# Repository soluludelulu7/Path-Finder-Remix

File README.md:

Path Finder Remix by Svanik

Description:
Made a PCB Schematic with 5 LED's, 5 buttons, 5 resistors, and a XIAO. Then, converted schematic into PCB; routed lines and added 3D files to create a complete image. Also, wrote the code to make the LED blink 5 times when the button is pressed. My motivation to make this project was to learn PCB design and desgin my own PCB from scratch. I learned everything I know abut PCB design from this project and it was a very fun experience.

| Name      | Purpose                              | Quantity | Total Cost (USD) | Link | Distributor |
|-----------|--------------------------------------|----------|------------------|------|-------------|
| Resistors | to restrict flow of current (not buying) | 1 | $5.99 | https://www.amazon.com/Resistor-Resistors-Assortment-Breadboard-Electronics/dp/B0F4P352BB | Amazon |
| LED       | to display (not buying)             | 1 | $7.99 | https://www.microcenter.com/product/427703/5mm_Round_Multi-Colored_LED_Assortment_Set_-_25_Pack | Microcenter |
| PCB       | to solder on                        | 5 | $4.90 | https://jlcpcb.com/ | JLCPCB |
| Buttons   | to click                            | 10 | $4.99 | https://www.amazon.com/BlingKingdom-Replacement-Mechanical-Keyboard-Dustproof/dp/B0DSHTPSL3 | Amazon |
| XIAO      | to control                          | 1 | $9.99 | https://www.amazon.com/Microcontroller-Dual-Core-MicroPython-CircuitPython-Interfaces/dp/B09NNVNW7M | Amazon |

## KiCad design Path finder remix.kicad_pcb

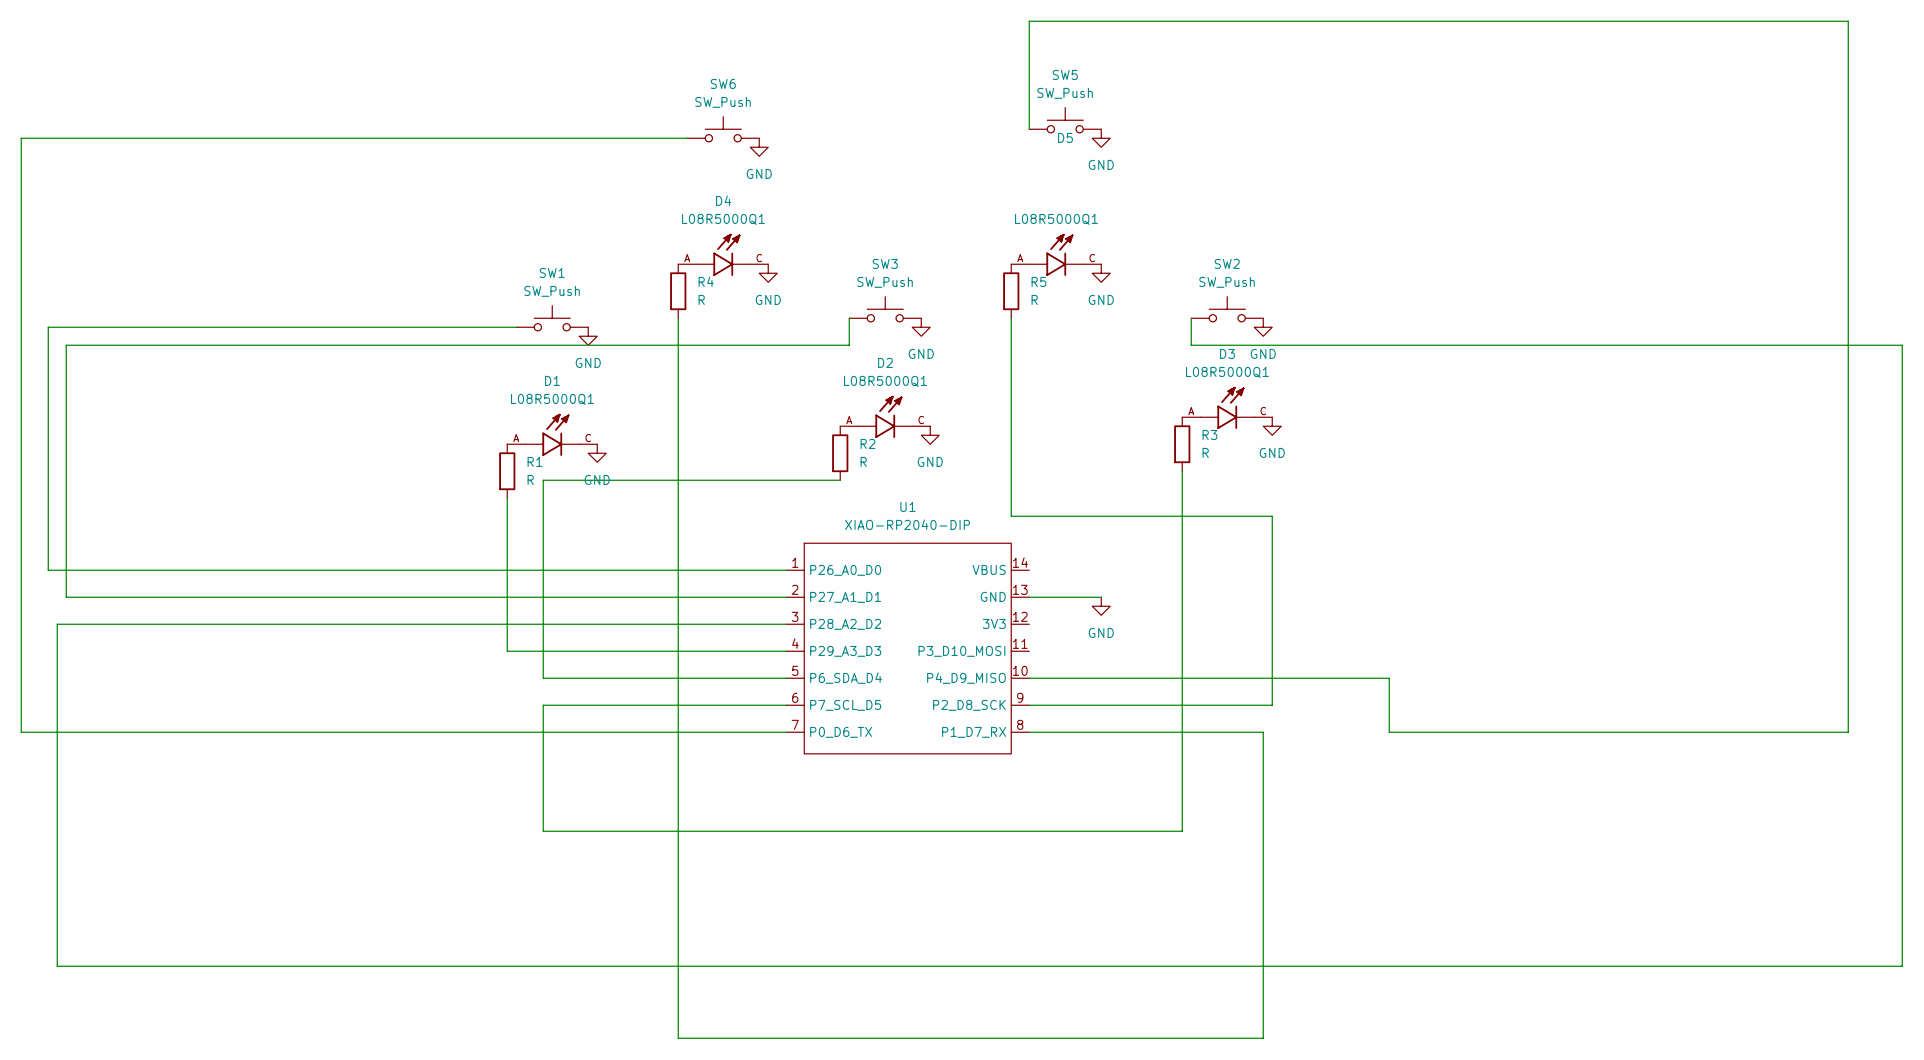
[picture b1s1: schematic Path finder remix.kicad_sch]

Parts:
D1, D2, D3, D4, D5: L08R5000Q1; LEDRD254W57D500H1070; PARTREV NA
R1, R2, R3, R4, R5: R; R_Axial_DIN0204_L3.6mm_D1.6mm_P5.08mm_Horizontal
SW1, SW2, SW3, SW5, SW6: SW_Push; SW_Cherry_MX_1.00u_PCB
U1: XIAO-RP2040-DIP

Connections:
GND: D1.C, D2.C, D3.C, D4.C, D5.C, SW1.2, SW2.2, SW3.2, SW5.2, SW6.2, U1.13 (GND)
unnamed: D1.A, R1.1
unnamed: D2.A, R2.1
unnamed: D3.A, R3.1
unnamed: D4.A, R4.1
unnamed: D5.A, R5.1
unnamed: SW6.1, U1.7 (P0_D6_TX)
unnamed: R4.2, U1.8 (P1_D7_RX)
unnamed: R5.2, U1.9 (P2_D8_SCK)
unnamed: SW5.1, U1.10 (P4_D9_MISO)
unnamed: R2.2, U1.5 (P6_SDA_D4)
unnamed: R3.2, U1.6 (P7_SCL_D5)
unnamed: SW1.1, U1.1 (P26_A0_D0)
unnamed: SW3.1, U1.2 (P27_A1_D1)
unnamed: SW2.1, U1.3 (P28_A2_D2)
unnamed: R1.2, U1.4 (P29_A3_D3)

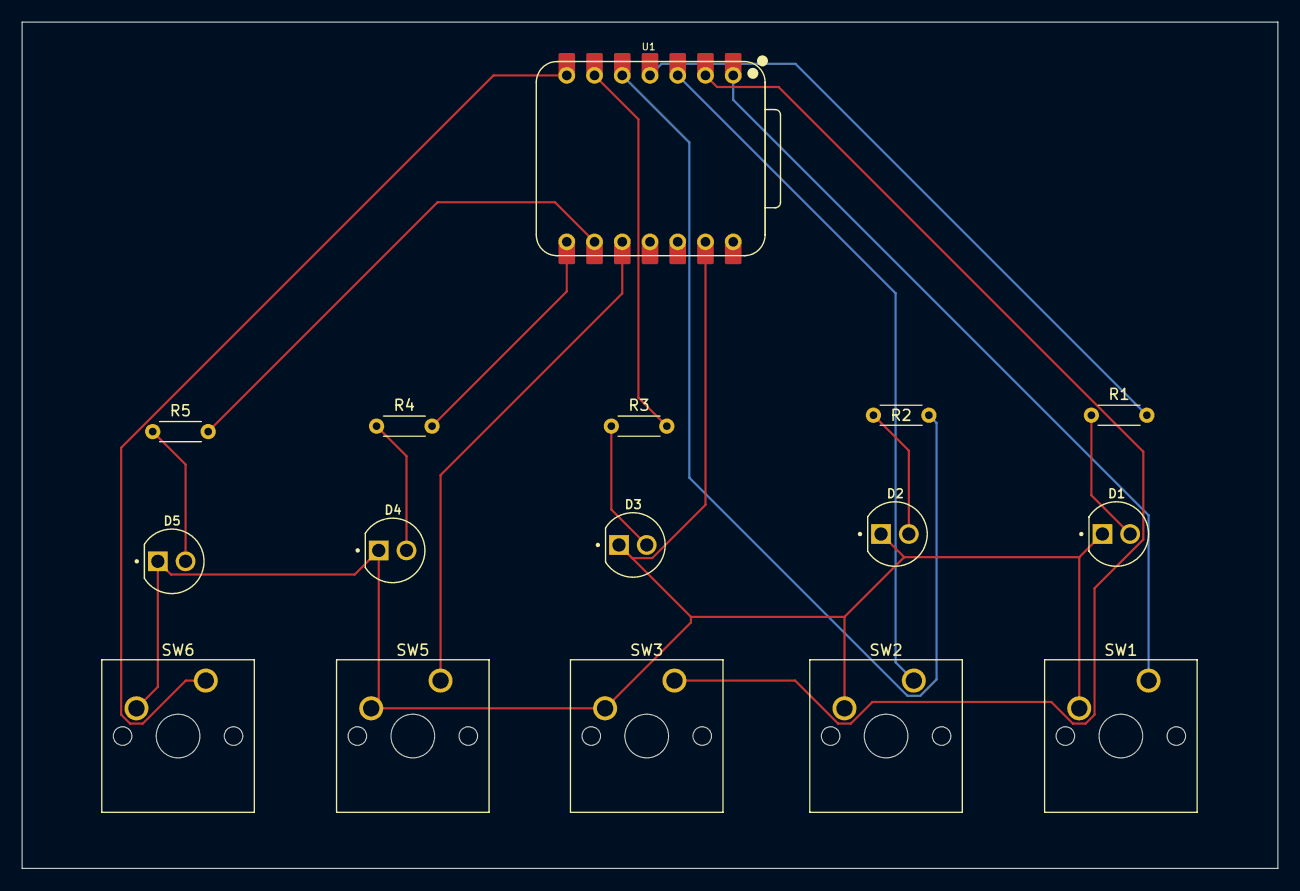
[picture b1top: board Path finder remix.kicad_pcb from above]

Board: 2 copper layers, 115.0 x 77.5 mm, 16 parts (0 on the bottom side), 16 nets.

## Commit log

2026-06-11 Update README with project details and images
    Added project overview, journal entries, and images for PCB design.
2026-06-12 Revise README with project details and component links
    Updated project overview and added a detailed description of the PCB design process. Included links for components used in the project.
2026-06-18 Revise README with new images and project details
    Updated images in the README and revised project description for clarity.
